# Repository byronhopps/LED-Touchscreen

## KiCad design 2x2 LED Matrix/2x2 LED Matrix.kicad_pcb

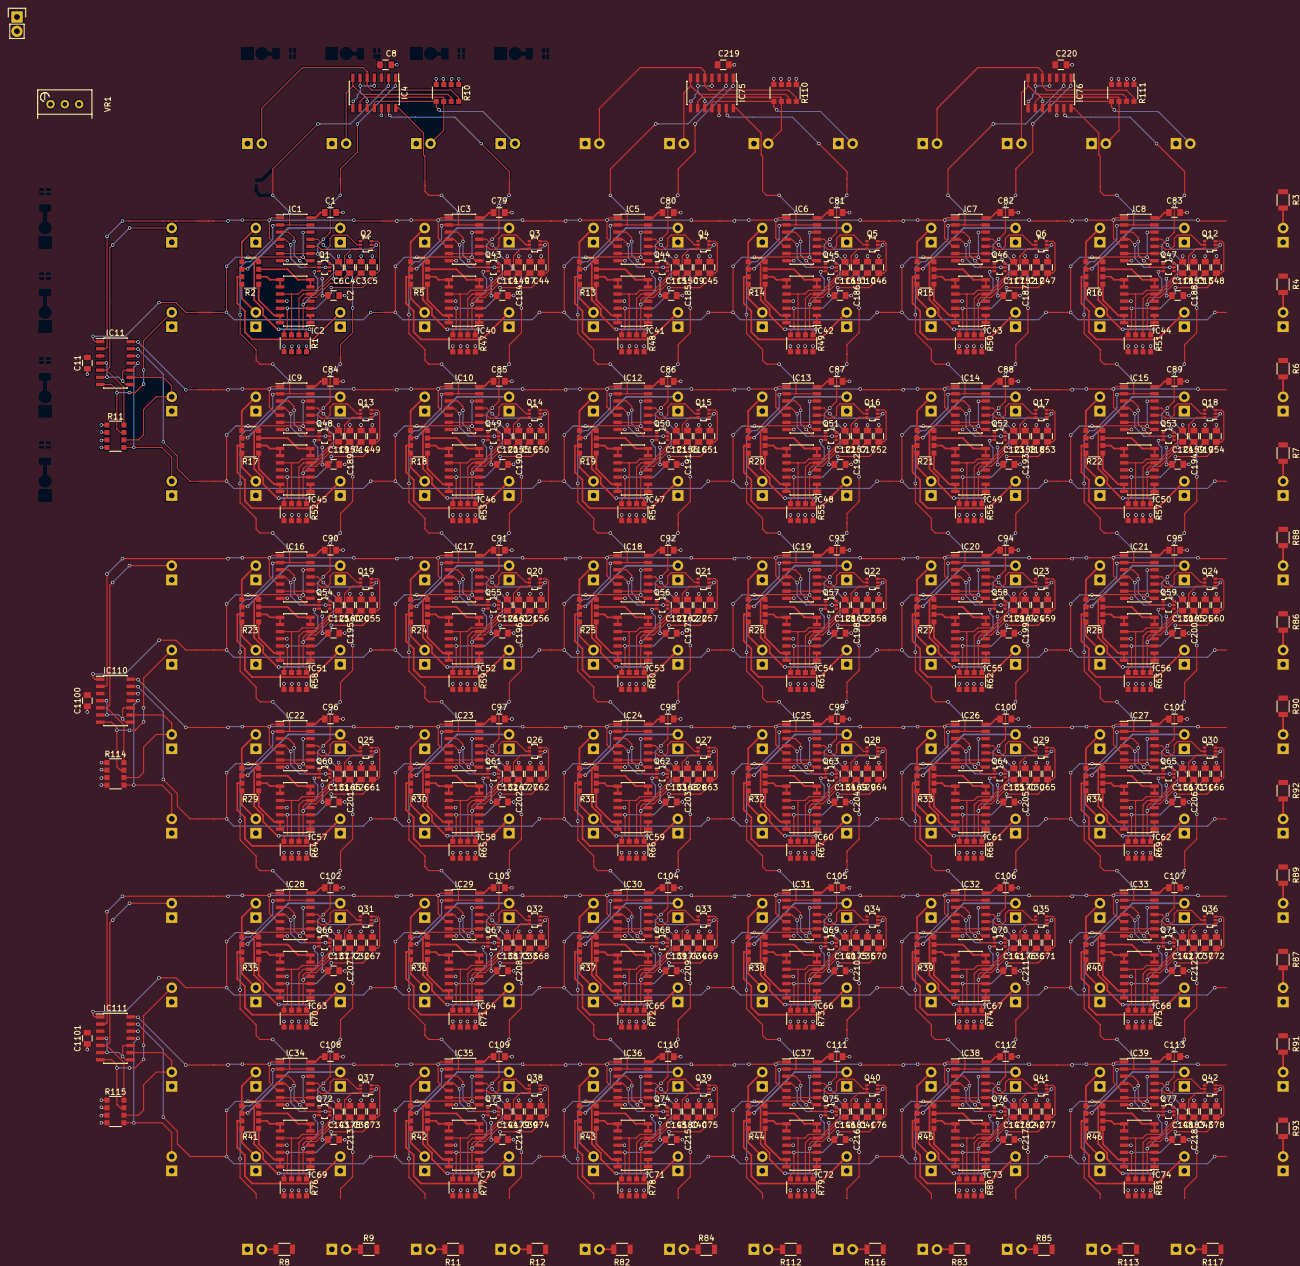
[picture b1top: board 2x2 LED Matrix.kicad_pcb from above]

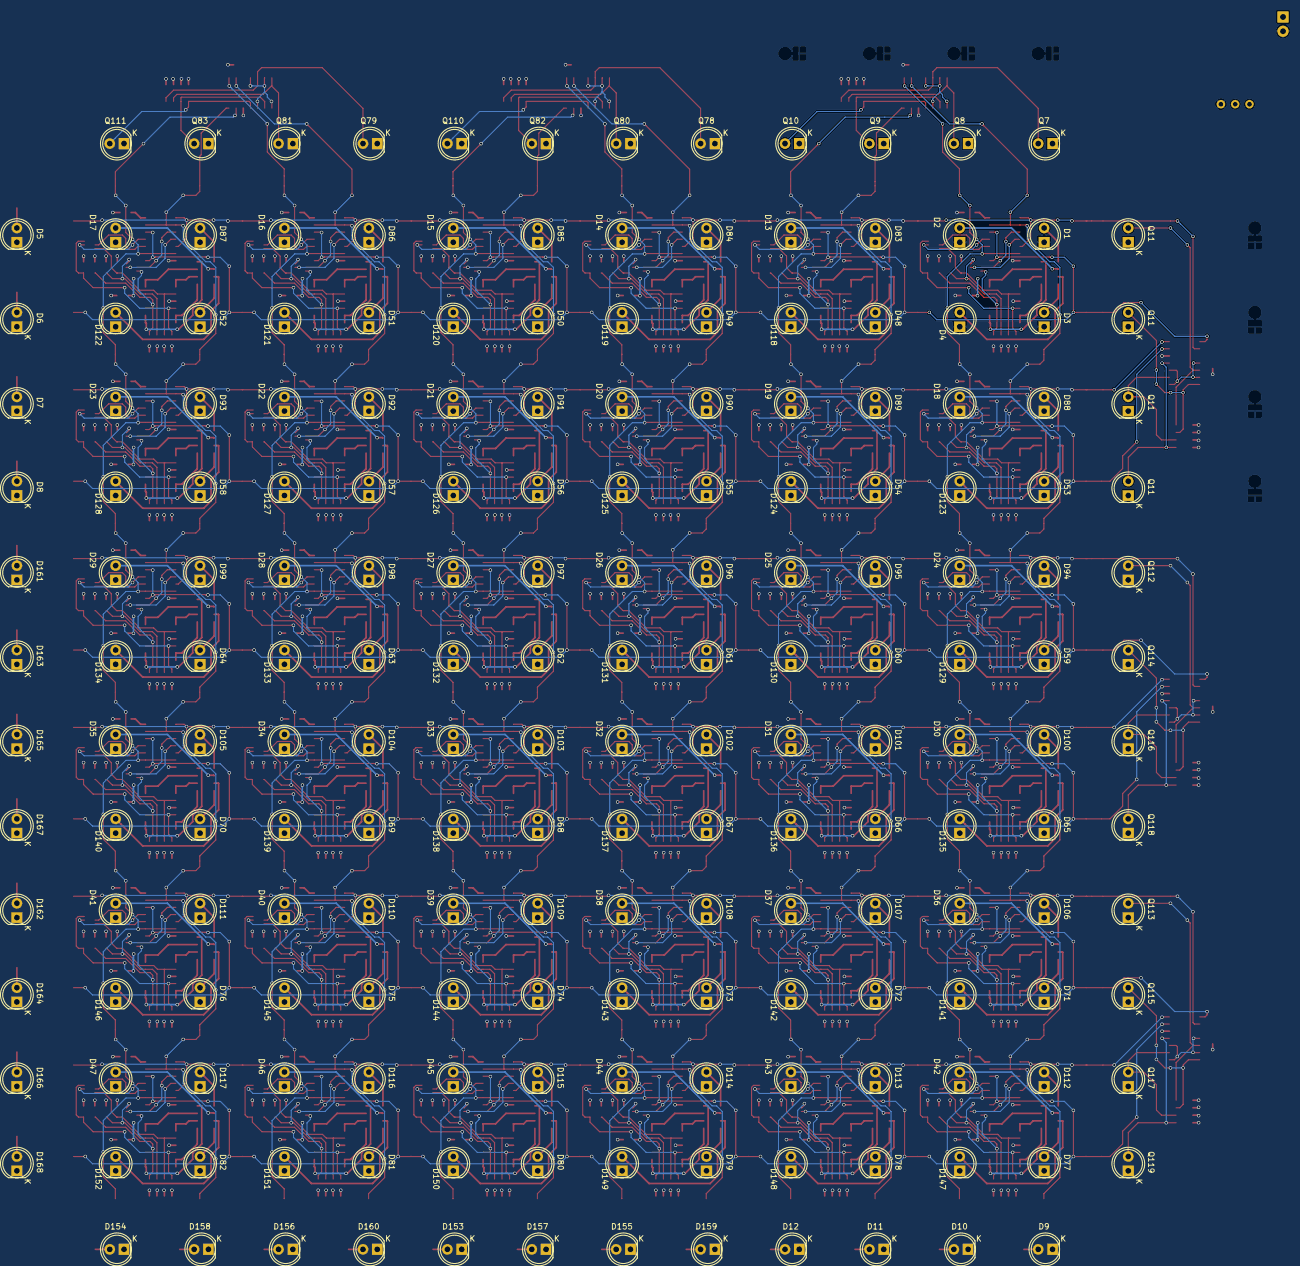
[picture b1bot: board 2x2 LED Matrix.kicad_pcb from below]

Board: 2 copper layers, 668 parts (192 on the bottom side), 47 nets.

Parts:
C1, C2, C8, C11, C79, C80, C81, C82, C83, C84, C85, C86, C87, C88, C89, C90, C91, C92, C93, C94, C95, C96, C97, C98, C99, C100, C101, C102, C103, C104, C105, C106, C107, C108, C109, C110, C111, C112, C113, C184, C185, C186, C187, C188, C189, C190, C191, C192, C193, C194, C195, C196, C197, C198, C199, C200, C201, C202, C203, C204, C205, C206, C207, C208, C209, C210, C211, C212, C213, C214, C215, C216, C217, C218, C219, C220, C1100, C1101: 100nF; C_0805
C3, C4, C5, C6, C7, C9, C10, C12, C13, C14, C15, C16, C17, C18, C19, C20, C21, C22, C23, C24, C25, C26, C27, C28, C29, C30, C31, C32, C33, C34, C35, C36, C37, C38, C39, C40, C41, C42, C43, C44, C45, C46, C47, C48, C49, C50, C51, C52, C53, C54, C55, C56, C57, C58, C59, C60, C61, C62, C63, C64, C65, C66, C67, C68, C69, C70, C71, C72, C73, C74, C75, C76, C77, C78, C114, C115, C116, C117, C118, C119, C120, C121, C122, C123, C124, C125, C126, C127, C128, C129, C130, C131, C132, C133, C134, C135, C136, C137, C138, C139, C140, C141, C142, C143, C144, C145, C146, C147, C148, C149, C150, C151, C152, C153, C154, C155, C156, C157, C158, C159, C160, C161, C162, C163, C164, C165, C166, C167, C168, C169, C170, C171, C172, C173, C174, C175, C176, C177, C178, C179, C180, C181, C182, C183: 1uF; C_0805
D1, D2, D3, D4, D13, D14, D15, D16, D17, D18, D19, D20, D21, D22, D23, D24, D25, D26, D27, D28, D29, D30, D31, D32, D33, D34, D35, D36, D37, D38, D39, D40, D41, D42, D43, D44, D45, D46, D47, D48, D49, D50, D51, D52, D53, D54, D55, D56, D57, D58, D59, D60, D61, D62, D63, D64, D65, D66, D67, D68, D69, D70, D71, D72, D73, D74, D75, D76, D77, D78, D79, D80, D81, D82, D83, D84, D85, D86, D87, D88, D89, D90, D91, D92, D93, D94, D95, D96, D97, D98, D99, D100, D101, D102, D103, D104, D105, D106, D107, D108, D109, D110, D111, D112, D113, D114, D115, D116, D117, D118, D119, D120, D121, D122, D123, D124, D125, D126, D127, D128, D129, D130, D131, D132, D133, D134, D135, D136, D137, D138, D139, D140, D141, D142, D143, D144, D145, D146, D147, D148, D149, D150, D151, D152: LED; LED-5MM
D5, D6, D7, D8, D9, D10, D11, D12, D153, D154, D155, D156, D157, D158, D159, D160, D161, D162, D163, D164, D165, D166, D167, D168: 850nm; LED-5MM
IC1, IC3, IC5, IC6, IC7, IC8, IC9, IC10, IC12, IC13, IC14, IC15, IC16, IC17, IC18, IC19, IC20, IC21, IC22, IC23, IC24, IC25, IC26, IC27, IC28, IC29, IC30, IC31, IC32, IC33, IC34, IC35, IC36, IC37, IC38, IC39: 4011; SOIC-14_3.9x8.7mm_Pitch1.27mm
IC2, IC40, IC41, IC42, IC43, IC44, IC45, IC46, IC47, IC48, IC49, IC50, IC51, IC52, IC53, IC54, IC55, IC56, IC57, IC58, IC59, IC60, IC61, IC62, IC63, IC64, IC65, IC66, IC67, IC68, IC69, IC70, IC71, IC72, IC73, IC74: LM324; SOIC-14_3.9x8.7mm_Pitch1.27mm
IC4, IC11, IC75, IC76, IC110, IC111: LM2901; SOIC-14_3.9x8.7mm_Pitch1.27mm
P1: PWR; Pin_Header_Straight_1x02
Q1, Q2, Q3, Q4, Q5, Q6, Q12, Q13, Q14, Q15, Q16, Q17, Q18, Q19, Q20, Q21, Q22, Q23, Q24, Q25, Q26, Q27, Q28, Q29, Q30, Q31, Q32, Q33, Q34, Q35, Q36, Q37, Q38, Q39, Q40, Q41, Q42, Q43, Q44, Q45, Q46, Q47, Q48, Q49, Q50, Q51, Q52, Q53, Q54, Q55, Q56, Q57, Q58, Q59, Q60, Q61, Q62, Q63, Q64, Q65, Q66, Q67, Q68, Q69, Q70, Q71, Q72, Q73, Q74, Q75, Q76, Q77: PMOS; TO-263
Q7, Q8, Q9, Q10, Q11, Q11#2, Q11#3, Q11#4, Q78, Q79, Q80, Q81, Q82, Q83, Q110, Q111, Q112, Q113, Q114, Q115, Q116, Q117, Q118, Q119: 850nm; LED-5MM
R1, R47, R48, R49, R50, R51, R52, R53, R54, R55, R56, R57, R58, R59, R60, R61, R62, R63, R64, R65, R66, R67, R68, R69, R70, R71, R72, R73, R74, R75, R76, R77, R78, R79, R80, R81: 220K; R_Array_Convex_4x1206
R2, R5, R13, R14, R15, R16, R17, R18, R19, R20, R21, R22, R23, R24, R25, R26, R27, R28, R29, R30, R31, R32, R33, R34, R35, R36, R37, R38, R39, R40, R41, R42, R43, R44, R45, R46: 470R; R_Array_Convex_4x1206
R3, R4, R6, R7, R8, R9, R11#2, R12, R82, R83, R84, R85, R86, R87, R88, R89, R90, R91, R92, R93, R112, R113, R116, R117: 120R; R_1206
R10, R11, R110, R111, R114, R115: 1K; R_Array_Convex_4x1206
VR1: 10K; Potentiometer_Bourns_3296W_3-8Zoll_Inline_ScrewUp

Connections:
+5V: C1.1, C2.1, C8.1, C11.1, C79.1, C80.1, C81.1, C82.1, C83.1, C84.1, C85.1, C86.1, C87.1, C88.1, C89.1, C90.1, C91.1, C92.1, C93.1, C94.1, C95.1, C96.1, C97.1, C98.1, C99.1, C100.1, C101.1, C102.1, C103.1, C104.1, C105.1, C106.1, C107.1, C108.1, C109.1, C110.1, C111.1, C112.1, C113.1, C184.1, C185.1, C186.1, C187.1, C188.1, C189.1, C190.1, C191.1, C192.1, C193.1, C194.1, C195.1, C196.1, C197.1, C198.1, C199.1, C200.1, C201.1, C202.1, C203.1, C204.1, C205.1, C206.1, C207.1, C208.1, C209.1, C210.1, C211.1, C212.1, C213.1, C214.1, C215.1, C216.1, C217.1, C218.1, C219.1, C220.1, C1100.1, C1101.1, IC1.14, IC2.4, IC3.14, IC4.3, IC5.14, IC6.14, IC7.14, IC8.14, IC9.14, IC10.14, IC11.3, IC12.14, IC13.14, IC14.14, IC15.14, IC16.14, IC17.14, IC18.14, IC19.14, IC20.14, IC21.14, IC22.14, IC23.14, IC24.14, IC25.14, IC26.14, IC27.14, IC28.14, IC29.14, IC30.14, IC31.14, IC32.14, IC33.14, IC34.14, IC35.14, IC36.14, IC37.14, IC38.14, IC39.14, IC40.4, IC41.4, IC42.4, IC43.4, IC44.4, IC45.4, IC46.4, IC47.4, IC48.4, IC49.4, IC50.4, IC51.4, IC52.4, IC53.4, IC54.4, IC55.4, IC56.4, IC57.4, IC58.4, IC59.4, IC60.4, IC61.4, IC62.4, IC63.4, IC64.4, IC65.4, IC66.4, IC67.4, IC68.4, IC69.4, IC70.4, IC71.4, IC72.4, IC73.4, IC74.4, IC75.3, IC76.3, IC110.3, IC111.3, P1.1, Q1.1, Q1.4, Q2.1, Q2.4, Q3.1, Q3.4, Q4.1, Q4.4, Q5.1, Q5.4, Q6.1, Q6.4, Q7.1, Q8.1, Q9.1, Q10.1, Q11.1, Q11#2.1, Q11#3.1, Q11#4.1, Q12.1, Q12.4, Q13.1, Q13.4, Q14.1, Q14.4, Q15.1, Q15.4, Q16.1, Q16.4, Q17.1, Q17.4, Q18.1, Q18.4, Q19.1, Q19.4, Q20.1, Q20.4, Q21.1, Q21.4, Q22.1, Q22.4, Q23.1, Q23.4, Q24.1, Q24.4, Q25.1, Q25.4, Q26.1, Q26.4, Q27.1, Q27.4, Q28.1, Q28.4, Q29.1, Q29.4, Q30.1, Q30.4, Q31.1, Q31.4, Q32.1, Q32.4, Q33.1, Q33.4, Q34.1, Q34.4, Q35.1, Q35.4, Q36.1, Q36.4, Q37.1, Q37.4, Q38.1, Q38.4, Q39.1, Q39.4, Q40.1, Q40.4, Q41.1, Q41.4, Q42.1, Q42.4, Q43.1, Q43.4, Q44.1, Q44.4, Q45.1, Q45.4, Q46.1, Q46.4, Q47.1, Q47.4, Q48.1, Q48.4, Q49.1, Q49.4, Q50.1, Q50.4, Q51.1, Q51.4, Q52.1, Q52.4, Q53.1, Q53.4, Q54.1, Q54.4, Q55.1, Q55.4, Q56.1, Q56.4, Q57.1, Q57.4, Q58.1, Q58.4, Q59.1, Q59.4, Q60.1, Q60.4, Q61.1, Q61.4, Q62.1, Q62.4, Q63.1, Q63.4, Q64.1, Q64.4, Q65.1, Q65.4, Q66.1, Q66.4, Q67.1, Q67.4, Q68.1, Q68.4, Q69.1, Q69.4, Q70.1, Q70.4, Q71.1, Q71.4, Q72.1, Q72.4, Q73.1, Q73.4, Q74.1, Q74.4, Q75.1, Q75.4, Q76.1, Q76.4, Q77.1, Q77.4, Q78.1, Q79.1, Q80.1, Q81.1, Q82.1, Q83.1, Q110.1, Q111.1, Q112.1, Q113.1, Q114.1, Q115.1, Q116.1, Q117.1, Q118.1, Q119.1, R3.1, R4.1, R6.1, R7.1, R8.1, R9.1, R11#2.1, R12.1, R82.1, R83.1, R84.1, R85.1, R86.1, R87.1, R88.1, R89.1, R90.1, R91.1, R92.1, R93.1, R112.1, R113.1, R116.1, R117.1, VR1.1
/Decay-1: C3.1, C7.1, C9.1, C10.1, C12.1, C13.1, C14.1, C15.1, C16.1, C17.1, C18.1, C19.1, C20.1, C21.1, C22.1, C23.1, C24.1, C25.1, C26.1, C27.1, C28.1, C29.1, C30.1, C31.1, C32.1, C33.1, C34.1, C35.1, C36.1, C37.1, C38.1, C39.1, C40.1, C41.1, C42.1, C43.1, IC2.3, IC40.3, IC41.3, IC42.3, IC43.3, IC44.3, IC45.3, IC46.3, IC47.3, IC48.3, IC49.3, IC50.3, IC51.3, IC52.3, IC53.3, IC54.3, IC55.3, IC56.3, IC57.3, IC58.3, IC59.3, IC60.3, IC61.3, IC62.3, IC63.3, IC64.3, IC65.3, IC66.3, IC67.3, IC68.3, IC69.3, IC70.3, IC71.3, IC72.3, IC73.3, IC74.3, Q1.3, Q43.3, Q44.3, Q45.3, Q46.3, Q47.3, Q48.3, Q49.3, Q50.3, Q51.3, Q52.3, Q53.3, Q54.3, Q55.3, Q56.3, Q57.3, Q58.3, Q59.3, Q60.3, Q61.3, Q62.3, Q63.3, Q64.3, Q65.3, Q66.3, Q67.3, Q68.3, Q69.3, Q70.3, Q71.3, Q72.3, Q73.3, Q74.3, Q75.3, Q76.3, Q77.3, R1.1, R47.1, R48.1, R49.1, R50.1, R51.1, R52.1, R53.1, R54.1, R55.1, R56.1, R57.1, R58.1, R59.1, R60.1, R61.1, R62.1, R63.1, R64.1, R65.1, R66.1, R67.1, R68.1, R69.1, R70.1, R71.1, R72.1, R73.1, R74.1, R75.1, R76.1, R77.1, R78.1, R79.1, R80.1, R81.1
/Decay-2: C4.1, C149.1, C150.1, C151.1, C152.1, C153.1, C154.1, C155.1, C156.1, C157.1, C158.1, C159.1, C160.1, C161.1, C162.1, C163.1, C164.1, C165.1, C166.1, C167.1, C168.1, C169.1, C170.1, C171.1, C172.1, C173.1, C174.1, C175.1, C176.1, C177.1, C178.1, C179.1, C180.1, C181.1, C182.1, C183.1, IC2.5, IC40.5, IC41.5, IC42.5, IC43.5, IC44.5, IC45.5, IC46.5, IC47.5, IC48.5, IC49.5, IC50.5, IC51.5, IC52.5, IC53.5, IC54.5, IC55.5, IC56.5, IC57.5, IC58.5, IC59.5, IC60.5, IC61.5, IC62.5, IC63.5, IC64.5, IC65.5, IC66.5, IC67.5, IC68.5, IC69.5, IC70.5, IC71.5, IC72.5, IC73.5, IC74.5, Q1.6, Q43.6, Q44.6, Q45.6, Q46.6, Q47.6, Q48.6, Q49.6, Q50.6, Q51.6, Q52.6, Q53.6, Q54.6, Q55.6, Q56.6, Q57.6, Q58.6, Q59.6, Q60.6, Q61.6, Q62.6, Q63.6, Q64.6, Q65.6, Q66.6, Q67.6, Q68.6, Q69.6, Q70.6, Q71.6, Q72.6, Q73.6, Q74.6, Q75.6, Q76.6, Q77.6, R1.2, R47.2, R48.2, R49.2, R50.2, R51.2, R52.2, R53.2, R54.2, R55.2, R56.2, R57.2, R58.2, R59.2, R60.2, R61.2, R62.2, R63.2, R64.2, R65.2, R66.2, R67.2, R68.2, R69.2, R70.2, R71.2, R72.2, R73.2, R74.2, R75.2, R76.2, R77.2, R78.2, R79.2, R80.2, R81.2
/Decay-3: C5.1, C44.1, C45.1, C46.1, C47.1, C48.1, C49.1, C50.1, C51.1, C52.1, C53.1, C54.1, C55.1, C56.1, C57.1, C58.1, C59.1, C60.1, C61.1, C62.1, C63.1, C64.1, C65.1, C66.1, C67.1, C68.1, C69.1, C70.1, C71.1, C72.1, C73.1, C74.1, C75.1, C76.1, C77.1, C78.1, IC2.12, IC40.12, IC41.12, IC42.12, IC43.12, IC44.12, IC45.12, IC46.12, IC47.12, IC48.12, IC49.12, IC50.12, IC51.12, IC52.12, IC53.12, IC54.12, IC55.12, IC56.12, IC57.12, IC58.12, IC59.12, IC60.12, IC61.12, IC62.12, IC63.12, IC64.12, IC65.12, IC66.12, IC67.12, IC68.12, IC69.12, IC70.12, IC71.12, IC72.12, IC73.12, IC74.12, Q2.3, Q3.3, Q4.3, Q5.3, Q6.3, Q12.3, Q13.3, Q14.3, Q15.3, Q16.3, Q17.3, Q18.3, Q19.3, Q20.3, Q21.3, Q22.3, Q23.3, Q24.3, Q25.3, Q26.3, Q27.3, Q28.3, Q29.3, Q30.3, Q31.3, Q32.3, Q33.3, Q34.3, Q35.3, Q36.3, Q37.3, Q38.3, Q39.3, Q40.3, Q41.3, Q42.3, R1.4, R47.4, R48.4, R49.4, R50.4, R51.4, R52.4, R53.4, R54.4, R55.4, R56.4, R57.4, R58.4, R59.4, R60.4, R61.4, R62.4, R63.4, R64.4, R65.4, R66.4, R67.4, R68.4, R69.4, R70.4, R71.4, R72.4, R73.4, R74.4, R75.4, R76.4, R77.4, R78.4, R79.4, R80.4, R81.4
/Decay-4: C6.1, C114.1, C115.1, C116.1, C117.1, C118.1, C119.1, C120.1, C121.1, C122.1, C123.1, C124.1, C125.1, C126.1, C127.1, C128.1, C129.1, C130.1, C131.1, C132.1, C133.1, C134.1, C135.1, C136.1, C137.1, C138.1, C139.1, C140.1, C141.1, C142.1, C143.1, C144.1, C145.1, C146.1, C147.1, C148.1, IC2.10, IC40.10, IC41.10, IC42.10, IC43.10, IC44.10, IC45.10, IC46.10, IC47.10, IC48.10, IC49.10, IC50.10, IC51.10, IC52.10, IC53.10, IC54.10, IC55.10, IC56.10, IC57.10, IC58.10, IC59.10, IC60.10, IC61.10, IC62.10, IC63.10, IC64.10, IC65.10, IC66.10, IC67.10, IC68.10, IC69.10, IC70.10, IC71.10, IC72.10, IC73.10, IC74.10, Q2.6, Q3.6, Q4.6, Q5.6, Q6.6, Q12.6, Q13.6, Q14.6, Q15.6, Q16.6, Q17.6, Q18.6, Q19.6, Q20.6, Q21.6, Q22.6, Q23.6, Q24.6, Q25.6, Q26.6, Q27.6, Q28.6, Q29.6, Q30.6, Q31.6, Q32.6, Q33.6, Q34.6, Q35.6, Q36.6, Q37.6, Q38.6, Q39.6, Q40.6, Q41.6, Q42.6, R1.3, R47.3, R48.3, R49.3, R50.3, R51.3, R52.3, R53.3, R54.3, R55.3, R56.3, R57.3, R58.3, R59.3, R60.3, R61.3, R62.3, R63.3, R64.3, R65.3, R66.3, R67.3, R68.3, R69.3, R70.3, R71.3, R72.3, R73.3, R74.3, R75.3, R76.3, R77.3, R78.3, R79.3, R80.3, R81.3
/Detector X/Detect-1: IC4.5, IC75.5, IC76.5, Q7.2, Q78.2, Q79.2, R10.8, R110.8, R111.8
/Detector X/Detect-2: IC4.7, IC75.7, IC76.7, Q8.2, Q80.2, Q81.2, R10.7, R110.7, R111.7
/Detector X/Detect-3: IC4.9, IC75.9, IC76.9, Q9.2, Q82.2, Q83.2, R10.6, R110.6, R111.6
/Detector X/Detect-4: IC4.11, IC75.11, IC76.11, Q10.2, Q110.2, Q111.2, R10.5, R110.5, R111.5
/Detector X/Out-1: IC4.2, IC75.2, IC76.2
/Detector X/Out-2: IC4.1, IC75.1, IC76.1
/Detector X/Out-3: IC4.14, IC75.14, IC76.14
/Detector X/Out-4: IC4.13, IC75.13, IC76.13
/Detector Y/Detect-1: IC11.5, IC110.5, IC111.5, Q11.2, Q112.2, Q113.2, R11.8, R114.8, R115.8
/Detector Y/Detect-2: IC11.7, IC110.7, IC111.7, Q11#2.2, Q114.2, Q115.2, R11.7, R114.7, R115.7
/Detector Y/Detect-3: IC11.9, IC110.9, IC111.9, Q11#3.2, Q116.2, Q117.2, R11.6, R114.6, R115.6
/Detector Y/Detect-4: IC11.11, IC110.11, IC111.11, Q11#4.2, Q118.2, Q119.2, R11.5, R114.5, R115.5
/Detector Y/Out-1: IC11.2, IC110.2, IC111.2
/Detector Y/Out-2: IC11.1, IC110.1, IC111.1
/Detector Y/Out-3: IC11.14, IC110.14, IC111.14
/Detector Y/Out-4: IC11.13, IC110.13, IC111.13
/LED1: IC2.1, IC2.2, IC40.1, IC40.2, IC41.1, IC41.2, IC42.1, IC42.2, IC43.1, IC43.2, IC44.1, IC44.2, IC45.1, IC45.2, IC46.1, IC46.2, IC47.1, IC47.2, IC48.1, IC48.2, IC49.1, IC49.2, IC50.1, IC50.2, IC51.1, IC51.2, IC52.1, IC52.2, IC53.1, IC53.2, IC54.1, IC54.2, IC55.1, IC55.2, IC56.1, IC56.2, IC57.1, IC57.2, IC58.1, IC58.2, IC59.1, IC59.2, IC60.1, IC60.2, IC61.1, IC61.2, IC62.1, IC62.2, IC63.1, IC63.2, IC64.1, IC64.2, IC65.1, IC65.2, IC66.1, IC66.2, IC67.1, IC67.2, IC68.1, IC68.2, IC69.1, IC69.2, IC70.1, IC70.2, IC71.1, IC71.2, IC72.1, IC72.2, IC73.1, IC73.2, IC74.1, IC74.2, R2.4, R5.4, R13.4, R14.4, R15.4, R16.4, R17.4, R18.4, R19.4, R20.4, R21.4, R22.4, R23.4, R24.4, R25.4, R26.4, R27.4, R28.4, R29.4, R30.4, R31.4, R32.4, R33.4, R34.4, R35.4, R36.4, R37.4, R38.4, R39.4, R40.4, R41.4, R42.4, R43.4, R44.4, R45.4, R46.4
/LED2: IC2.6, IC2.7, IC40.6, IC40.7, IC41.6, IC41.7, IC42.6, IC42.7, IC43.6, IC43.7, IC44.6, IC44.7, IC45.6, IC45.7, IC46.6, IC46.7, IC47.6, IC47.7, IC48.6, IC48.7, IC49.6, IC49.7, IC50.6, IC50.7, IC51.6, IC51.7, IC52.6, IC52.7, IC53.6, IC53.7, IC54.6, IC54.7, IC55.6, IC55.7, IC56.6, IC56.7, IC57.6, IC57.7, IC58.6, IC58.7, IC59.6, IC59.7, IC60.6, IC60.7, IC61.6, IC61.7, IC62.6, IC62.7, IC63.6, IC63.7, IC64.6, IC64.7, IC65.6, IC65.7, IC66.6, IC66.7, IC67.6, IC67.7, IC68.6, IC68.7, IC69.6, IC69.7, IC70.6, IC70.7, IC71.6, IC71.7, IC72.6, IC72.7, IC73.6, IC73.7, IC74.6, IC74.7, R2.3, R5.3, R13.3, R14.3, R15.3, R16.3, R17.3, R18.3, R19.3, R20.3, R21.3, R22.3, R23.3, R24.3, R25.3, R26.3, R27.3, R28.3, R29.3, R30.3, R31.3, R32.3, R33.3, R34.3, R35.3, R36.3, R37.3, R38.3, R39.3, R40.3, R41.3, R42.3, R43.3, R44.3, R45.3, R46.3
/LED3: IC2.13, IC2.14, IC40.13, IC40.14, IC41.13, IC41.14, IC42.13, IC42.14, IC43.13, IC43.14, IC44.13, IC44.14, IC45.13, IC45.14, IC46.13, IC46.14, IC47.13, IC47.14, IC48.13, IC48.14, IC49.13, IC49.14, IC50.13, IC50.14, IC51.13, IC51.14, IC52.13, IC52.14, IC53.13, IC53.14, IC54.13, IC54.14, IC55.13, IC55.14, IC56.13, IC56.14, IC57.13, IC57.14, IC58.13, IC58.14, IC59.13, IC59.14, IC60.13, IC60.14, IC61.13, IC61.14, IC62.13, IC62.14, IC63.13, IC63.14, IC64.13, IC64.14, IC65.13, IC65.14, IC66.13, IC66.14, IC67.13, IC67.14, IC68.13, IC68.14, IC69.13, IC69.14, IC70.13, IC70.14, IC71.13, IC71.14, IC72.13, IC72.14, IC73.13, IC73.14, IC74.13, IC74.14, R2.1, R5.1, R13.1, R14.1, R15.1, R16.1, R17.1, R18.1, R19.1, R20.1, R21.1, R22.1, R23.1, R24.1, R25.1, R26.1, R27.1, R28.1, R29.1, R30.1, R31.1, R32.1, R33.1, R34.1, R35.1, R36.1, R37.1, R38.1, R39.1, R40.1, R41.1, R42.1, R43.1, R44.1, R45.1, R46.1
/LED4: IC2.8, IC2.9, IC40.8, IC40.9, IC41.8, IC41.9, IC42.8, IC42.9, IC43.8, IC43.9, IC44.8, IC44.9, IC45.8, IC45.9, IC46.8, IC46.9, IC47.8, IC47.9, IC48.8, IC48.9, IC49.8, IC49.9, IC50.8, IC50.9, IC51.8, IC51.9, IC52.8, IC52.9, IC53.8, IC53.9, IC54.8, IC54.9, IC55.8, IC55.9, IC56.8, IC56.9, IC57.8, IC57.9, IC58.8, IC58.9, IC59.8, IC59.9, IC60.8, IC60.9, IC61.8, IC61.9, IC62.8, IC62.9, IC63.8, IC63.9, IC64.8, IC64.9, IC65.8, IC65.9, IC66.8, IC66.9, IC67.8, IC67.9, IC68.8, IC68.9, IC69.8, IC69.9, IC70.8, IC70.9, IC71.8, IC71.9, IC72.8, IC72.9, IC73.8, IC73.9, IC74.8, IC74.9, R2.2, R5.2, R13.2, R14.2, R15.2, R16.2, R17.2, R18.2, R19.2, R20.2, R21.2, R22.2, R23.2, R24.2, R25.2, R26.2, R27.2, R28.2, R29.2, R30.2, R31.2, R32.2, R33.2, R34.2, R35.2, R36.2, R37.2, R38.2, R39.2, R40.2, R41.2, R42.2, R43.2, R44.2, R45.2, R46.2
/On-1: IC1.3, IC3.3, IC5.3, IC6.3, IC7.3, IC8.3, IC9.3, IC10.3, IC12.3, IC13.3, IC14.3, IC15.3, IC16.3, IC17.3, IC18.3, IC19.3, IC20.3, IC21.3, IC22.3, IC23.3, IC24.3, IC25.3, IC26.3, IC27.3, IC28.3, IC29.3, IC30.3, IC31.3, IC32.3, IC33.3, IC34.3, IC35.3, IC36.3, IC37.3, IC38.3, IC39.3, Q1.2, Q43.2, Q44.2, Q45.2, Q46.2, Q47.2, Q48.2, Q49.2, Q50.2, Q51.2, Q52.2, Q53.2, Q54.2, Q55.2, Q56.2, Q57.2, Q58.2, Q59.2, Q60.2, Q61.2, Q62.2, Q63.2, Q64.2, Q65.2, Q66.2, Q67.2, Q68.2, Q69.2, Q70.2, Q71.2, Q72.2, Q73.2, Q74.2, Q75.2, Q76.2, Q77.2
/On-2: IC1.4, IC3.4, IC5.4, IC6.4, IC7.4, IC8.4, IC9.4, IC10.4, IC12.4, IC13.4, IC14.4, IC15.4, IC16.4, IC17.4, IC18.4, IC19.4, IC20.4, IC21.4, IC22.4, IC23.4, IC24.4, IC25.4, IC26.4, IC27.4, IC28.4, IC29.4, IC30.4, IC31.4, IC32.4, IC33.4, IC34.4, IC35.4, IC36.4, IC37.4, IC38.4, IC39.4, Q1.5, Q43.5, Q44.5, Q45.5, Q46.5, Q47.5, Q48.5, Q49.5, Q50.5, Q51.5, Q52.5, Q53.5, Q54.5, Q55.5, Q56.5, Q57.5, Q58.5, Q59.5, Q60.5, Q61.5, Q62.5, Q63.5, Q64.5, Q65.5, Q66.5, Q67.5, Q68.5, Q69.5, Q70.5, Q71.5, Q72.5, Q73.5, Q74.5, Q75.5, Q76.5, Q77.5
/On-3: IC1.11, IC3.11, IC5.11, IC6.11, IC7.11, IC8.11, IC9.11, IC10.11, IC12.11, IC13.11, IC14.11, IC15.11, IC16.11, IC17.11, IC18.11, IC19.11, IC20.11, IC21.11, IC22.11, IC23.11, IC24.11, IC25.11, IC26.11, IC27.11, IC28.11, IC29.11, IC30.11, IC31.11, IC32.11, IC33.11, IC34.11, IC35.11, IC36.11, IC37.11, IC38.11, IC39.11, Q2.2, Q3.2, Q4.2, Q5.2, Q6.2, Q12.2, Q13.2, Q14.2, Q15.2, Q16.2, Q17.2, Q18.2, Q19.2, Q20.2, Q21.2, Q22.2, Q23.2, Q24.2, Q25.2, Q26.2, Q27.2, Q28.2, Q29.2, Q30.2, Q31.2, Q32.2, Q33.2, Q34.2, Q35.2, Q36.2, Q37.2, Q38.2, Q39.2, Q40.2, Q41.2, Q42.2
/On-4: IC1.10, IC3.10, IC5.10, IC6.10, IC7.10, IC8.10, IC9.10, IC10.10, IC12.10, IC13.10, IC14.10, IC15.10, IC16.10, IC17.10, IC18.10, IC19.10, IC20.10, IC21.10, IC22.10, IC23.10, IC24.10, IC25.10, IC26.10, IC27.10, IC28.10, IC29.10, IC30.10, IC31.10, IC32.10, IC33.10, IC34.10, IC35.10, IC36.10, IC37.10, IC38.10, IC39.10, Q2.5, Q3.5, Q4.5, Q5.5, Q6.5, Q12.5, Q13.5, Q14.5, Q15.5, Q16.5, Q17.5, Q18.5, Q19.5, Q20.5, Q21.5, Q22.5, Q23.5, Q24.5, Q25.5, Q26.5, Q27.5, Q28.5, Q29.5, Q30.5, Q31.5, Q32.5, Q33.5, Q34.5, Q35.5, Q36.5, Q37.5, Q38.5, Q39.5, Q40.5, Q41.5, Q42.5
/X1: IC1.2, IC1.13, IC3.2, IC3.13, IC5.2, IC5.13, IC6.2, IC6.13, IC7.2, IC7.13, IC8.2, IC8.13, IC9.2, IC9.13, IC10.2, IC10.13, IC12.2, IC12.13, IC13.2, IC13.13, IC14.2, IC14.13, IC15.2, IC15.13, IC16.2, IC16.13, IC17.2, IC17.13, IC18.2, IC18.13, IC19.2, IC19.13, IC20.2, IC20.13, IC21.2, IC21.13, IC22.2, IC22.13, IC23.2, IC23.13, IC24.2, IC24.13, IC25.2, IC25.13, IC26.2, IC26.13, IC27.2, IC27.13, IC28.2, IC28.13, IC29.2, IC29.13, IC30.2, IC30.13, IC31.2, IC31.13, IC32.2, IC32.13, IC33.2, IC33.13, IC34.2, IC34.13, IC35.2, IC35.13, IC36.2, IC36.13, IC37.2, IC37.13, IC38.2, IC38.13, IC39.2, IC39.13
/X2: IC1.6, IC1.9, IC3.6, IC3.9, IC5.6, IC5.9, IC6.6, IC6.9, IC7.6, IC7.9, IC8.6, IC8.9, IC9.6, IC9.9, IC10.6, IC10.9, IC12.6, IC12.9, IC13.6, IC13.9, IC14.6, IC14.9, IC15.6, IC15.9, IC16.6, IC16.9, IC17.6, IC17.9, IC18.6, IC18.9, IC19.6, IC19.9, IC20.6, IC20.9, IC21.6, IC21.9, IC22.6, IC22.9, IC23.6, IC23.9, IC24.6, IC24.9, IC25.6, IC25.9, IC26.6, IC26.9, IC27.6, IC27.9, IC28.6, IC28.9, IC29.6, IC29.9, IC30.6, IC30.9, IC31.6, IC31.9, IC32.6, IC32.9, IC33.6, IC33.9, IC34.6, IC34.9, IC35.6, IC35.9, IC36.6, IC36.9, IC37.6, IC37.9, IC38.6, IC38.9, IC39.6, IC39.9
/Y1: IC1.1, IC1.5, IC3.1, IC3.5, IC5.1, IC5.5, IC6.1, IC6.5, IC7.1, IC7.5, IC8.1, IC8.5, IC9.1, IC9.5, IC10.1, IC10.5, IC12.1, IC12.5, IC13.1, IC13.5, IC14.1, IC14.5, IC15.1, IC15.5, IC16.1, IC16.5, IC17.1, IC17.5, IC18.1, IC18.5, IC19.1, IC19.5, IC20.1, IC20.5, IC21.1, IC21.5, IC22.1, IC22.5, IC23.1, IC23.5, IC24.1, IC24.5, IC25.1, IC25.5, IC26.1, IC26.5, IC27.1, IC27.5, IC28.1, IC28.5, IC29.1, IC29.5, IC30.1, IC30.5, IC31.1, IC31.5, IC32.1, IC32.5, IC33.1, IC33.5, IC34.1, IC34.5, IC35.1, IC35.5, IC36.1, IC36.5, IC37.1, IC37.5, IC38.1, IC38.5, IC39.1, IC39.5
/Y2: IC1.8, IC1.12, IC3.8, IC3.12, IC5.8, IC5.12, IC6.8, IC6.12, IC7.8, IC7.12, IC8.8, IC8.12, IC9.8, IC9.12, IC10.8, IC10.12, IC12.8, IC12.12, IC13.8, IC13.12, IC14.8, IC14.12, IC15.8, IC15.12, IC16.8, IC16.12, IC17.8, IC17.12, IC18.8, IC18.12, IC19.8, IC19.12, IC20.8, IC20.12, IC21.8, IC21.12, IC22.8, IC22.12, IC23.8, IC23.12, IC24.8, IC24.12, IC25.8, IC25.12, IC26.8, IC26.12, IC27.8, IC27.12, IC28.8, IC28.12, IC29.8, IC29.12, IC30.8, IC30.12, IC31.8, IC31.12, IC32.8, IC32.12, IC33.8, IC33.12, IC34.8, IC34.12, IC35.8, IC35.12, IC36.8, IC36.12, IC37.8, IC37.12, IC38.8, IC38.12, IC39.8, IC39.12
GND: C1.2, C2.2, C3.2, C4.2, C5.2, C6.2, C7.2, C8.2, C9.2, C10.2, C11.2, C12.2, C13.2, C14.2, C15.2, C16.2, C17.2, C18.2, C19.2, C20.2, C21.2, C22.2, C23.2, C24.2, C25.2, C26.2, C27.2, C28.2, C29.2, C30.2, C31.2, C32.2, C33.2, C34.2, C35.2, C36.2, C37.2, C38.2, C39.2, C40.2, C41.2, C42.2, C43.2, C44.2, C45.2, C46.2, C47.2, C48.2, C49.2, C50.2, C51.2, C52.2, C53.2, C54.2, C55.2, C56.2, C57.2, C58.2, C59.2, C60.2, C61.2, C62.2, C63.2, C64.2, C65.2, C66.2, C67.2, C68.2, C69.2, C70.2, C71.2, C72.2, C73.2, C74.2, C75.2, C76.2, C77.2, C78.2, C79.2, C80.2, C81.2, C82.2, C83.2, C84.2, C85.2, C86.2, C87.2, C88.2, C89.2, C90.2, C91.2, C92.2, C93.2, C94.2, C95.2, C96.2, C97.2, C98.2, C99.2, C100.2, C101.2, C102.2, C103.2, C104.2, C105.2, C106.2, C107.2, C108.2, C109.2, C110.2, C111.2, C112.2, C113.2, C114.2, C115.2, C116.2, C117.2, C118.2, C119.2, C120.2, C121.2, C122.2, C123.2, C124.2, C125.2, C126.2, C127.2, C128.2, C129.2, C130.2, C131.2, C132.2, C133.2, C134.2, C135.2, C136.2, C137.2, C138.2, C139.2, C140.2, C141.2, C142.2, C143.2, C144.2, C145.2, C146.2, C147.2, C148.2, C149.2, C150.2, C151.2, C152.2, C153.2, C154.2, C155.2, C156.2, C157.2, C158.2, C159.2, C160.2, C161.2, C162.2, C163.2, C164.2, C165.2, C166.2, C167.2, C168.2, C169.2, C170.2, C171.2, C172.2, C173.2, C174.2, C175.2, C176.2, C177.2, C178.2, C179.2, C180.2, C181.2, C182.2, C183.2, C184.2, C185.2, C186.2, C187.2, C188.2, C189.2, C190.2, C191.2, C192.2, C193.2, C194.2, C195.2, C196.2, C197.2, C198.2, C199.2, C200.2, C201.2, C202.2, C203.2, C204.2, C205.2, C206.2, C207.2, C208.2, C209.2, C210.2, C211.2, C212.2, C213.2, C214.2, C215.2, C216.2, C217.2, C218.2, C219.2, C220.2, C1100.2, C1101.2, D1.1, D2.1, D3.1, D4.1, D5.1, D6.1, D7.1, D8.1, D9.1, D10.1, D11.1, D12.1, D13.1, D14.1, D15.1, D16.1, D17.1, D18.1, D19.1, D20.1, D21.1, D22.1, D23.1, D24.1, D25.1, D26.1, D27.1, D28.1, D29.1, D30.1, D31.1, D32.1, D33.1, D34.1, D35.1, D36.1, D37.1, D38.1, D39.1, D40.1, D41.1, D42.1, D43.1, D44.1, D45.1, D46.1, D47.1, D48.1, D49.1, D50.1, D51.1, D52.1, D53.1, D54.1, D55.1, D56.1, D57.1, D58.1, D59.1, D60.1, D61.1, D62.1, D63.1, D64.1, D65.1, D66.1, D67.1, D68.1, D69.1, D70.1, D71.1, D72.1, D73.1, D74.1, D75.1, D76.1, D77.1, D78.1, D79.1, D80.1, D81.1, D82.1, D83.1, D84.1, D85.1, D86.1, D87.1, D88.1, D89.1, D90.1, D91.1, D92.1, D93.1, D94.1, D95.1, D96.1, D97.1, D98.1, D99.1, D100.1, D101.1, D102.1, D103.1, D104.1, D105.1, D106.1, D107.1, D108.1, D109.1, D110.1, D111.1, D112.1, D113.1, D114.1, D115.1, D116.1, D117.1, D118.1, D119.1, D120.1, D121.1, D122.1, D123.1, D124.1, D125.1, D126.1, D127.1, D128.1, D129.1, D130.1, D131.1, D132.1, D133.1, D134.1, D135.1, D136.1, D137.1, D138.1, D139.1, D140.1, D141.1, D142.1, D143.1, D144.1, D145.1, D146.1, D147.1, D148.1, D149.1, D150.1, D151.1, D152.1, D153.1, D154.1, D155.1, D156.1, D157.1, D158.1, D159.1, D160.1, D161.1, D162.1, D163.1, D164.1, D165.1, D166.1, D167.1, D168.1, IC1.7, IC2.11, IC3.7, IC4.12, IC5.7, IC6.7, IC7.7, IC8.7, IC9.7, IC10.7, IC11.12, IC12.7, IC13.7, IC14.7, IC15.7, IC16.7, IC17.7, IC18.7, IC19.7, IC20.7, IC21.7, IC22.7, IC23.7, IC24.7, IC25.7, IC26.7, IC27.7, IC28.7, IC29.7, IC30.7, IC31.7, IC32.7, IC33.7, IC34.7, IC35.7, IC36.7, IC37.7, IC38.7, IC39.7, IC40.11, IC41.11, IC42.11, IC43.11, IC44.11, IC45.11, IC46.11, IC47.11, IC48.11, IC49.11, IC50.11, IC51.11, IC52.11, IC53.11, IC54.11, IC55.11, IC56.11, IC57.11, IC58.11, IC59.11, IC60.11, IC61.11, IC62.11, IC63.11, IC64.11, IC65.11, IC66.11, IC67.11, IC68.11, IC69.11, IC70.11, IC71.11, IC72.11, IC73.11, IC74.11, IC75.12, IC76.12, IC110.12, IC111.12, P1.2, R1.5, R1.6, R1.7, R1.8, R10.1, R10.2, R10.3, R10.4, R11.1, R11.2, R11.3, R11.4, R47.5, R47.6, R47.7, R47.8, R48.5, R48.6, R48.7, R48.8, R49.5, R49.6, R49.7, R49.8, R50.5, R50.6, R50.7, R50.8, R51.5, R51.6, R51.7, R51.8, R52.5, R52.6, R52.7, R52.8, R53.5, R53.6, R53.7, R53.8, R54.5, R54.6, R54.7, R54.8, R55.5, R55.6, R55.7, R55.8, R56.5, R56.6, R56.7, R56.8, R57.5, R57.6, R57.7, R57.8, R58.5, R58.6, R58.7, R58.8, R59.5, R59.6, R59.7, R59.8, R60.5, R60.6, R60.7, R60.8, R61.5, R61.6, R61.7, R61.8, R62.5, R62.6, R62.7, R62.8, R63.5, R63.6, R63.7, R63.8, R64.5, R64.6, R64.7, R64.8, R65.5, R65.6, R65.7, R65.8, R66.5, R66.6, R66.7, R66.8, R67.5, R67.6, R67.7, R67.8, R68.5, R68.6, R68.7, R68.8, R69.5, R69.6, R69.7, R69.8, R70.5, R70.6, R70.7, R70.8, R71.5, R71.6, R71.7, R71.8, R72.5, R72.6, R72.7, R72.8, R73.5, R73.6, R73.7, R73.8, R74.5, R74.6, R74.7, R74.8, R75.5, R75.6, R75.7, R75.8, R76.5, R76.6, R76.7, R76.8, R77.5, R77.6, R77.7, R77.8, R78.5, R78.6, R78.7, R78.8, R79.5, R79.6, R79.7, R79.8, R80.5, R80.6, R80.7, R80.8, R81.5, R81.6, R81.7, R81.8, R110.1, R110.2, R110.3, R110.4, R111.1, R111.2, R111.3, R111.4, R114.1, R114.2, R114.3, R114.4, R115.1, R115.2, R115.3, R115.4, VR1.3
unnamed: D1.2, D83.2, D84.2, D85.2, D86.2, D87.2, D88.2, D89.2, D90.2, D91.2, D92.2, D93.2, D94.2, D95.2, D96.2, D97.2, D98.2, D99.2, D100.2, D101.2, D102.2, D103.2, D104.2, D105.2, D106.2, D107.2, D108.2, D109.2, D110.2, D111.2, D112.2, D113.2, D114.2, D115.2, D116.2, D117.2, R2.5, R5.5, R13.5, R14.5, R15.5, R16.5, R17.5, R18.5, R19.5, R20.5, R21.5, R22.5, R23.5, R24.5, R25.5, R26.5, R27.5, R28.5, R29.5, R30.5, R31.5, R32.5, R33.5, R34.5, R35.5, R36.5, R37.5, R38.5, R39.5, R40.5, R41.5, R42.5, R43.5, R44.5, R45.5, R46.5
unnamed: D2.2, D13.2, D14.2, D15.2, D16.2, D17.2, D18.2, D19.2, D20.2, D21.2, D22.2, D23.2, D24.2, D25.2, D26.2, D27.2, D28.2, D29.2, D30.2, D31.2, D32.2, D33.2, D34.2, D35.2, D36.2, D37.2, D38.2, D39.2, D40.2, D41.2, D42.2, D43.2, D44.2, D45.2, D46.2, D47.2, R2.6, R5.6, R13.6, R14.6, R15.6, R16.6, R17.6, R18.6, R19.6, R20.6, R21.6, R22.6, R23.6, R24.6, R25.6, R26.6, R27.6, R28.6, R29.6, R30.6, R31.6, R32.6, R33.6, R34.6, R35.6, R36.6, R37.6, R38.6, R39.6, R40.6, R41.6, R42.6, R43.6, R44.6, R45.6, R46.6
unnamed: D3.2, D48.2, D49.2, D50.2, D51.2, D52.2, D53.2, D54.2, D55.2, D56.2, D57.2, D58.2, D59.2, D60.2, D61.2, D62.2, D63.2, D64.2, D65.2, D66.2, D67.2, D68.2, D69.2, D70.2, D71.2, D72.2, D73.2, D74.2, D75.2, D76.2, D77.2, D78.2, D79.2, D80.2, D81.2, D82.2, R2.8, R5.8, R13.8, R14.8, R15.8, R16.8, R17.8, R18.8, R19.8, R20.8, R21.8, R22.8, R23.8, R24.8, R25.8, R26.8, R27.8, R28.8, R29.8, R30.8, R31.8, R32.8, R33.8, R34.8, R35.8, R36.8, R37.8, R38.8, R39.8, R40.8, R41.8, R42.8, R43.8, R44.8, R45.8, R46.8
unnamed: D4.2, D118.2, D119.2, D120.2, D121.2, D122.2, D123.2, D124.2, D125.2, D126.2, D127.2, D128.2, D129.2, D130.2, D131.2, D132.2, D133.2, D134.2, D135.2, D136.2, D137.2, D138.2, D139.2, D140.2, D141.2, D142.2, D143.2, D144.2, D145.2, D146.2, D147.2, D148.2, D149.2, D150.2, D151.2, D152.2, R2.7, R5.7, R13.7, R14.7, R15.7, R16.7, R17.7, R18.7, R19.7, R20.7, R21.7, R22.7, R23.7, R24.7, R25.7, R26.7, R27.7, R28.7, R29.7, R30.7, R31.7, R32.7, R33.7, R34.7, R35.7, R36.7, R37.7, R38.7, R39.7, R40.7, R41.7, R42.7, R43.7, R44.7, R45.7, R46.7
unnamed: D5.2, D161.2, D162.2, R3.2, R88.2, R89.2
unnamed: D6.2, D163.2, D164.2, R4.2, R86.2, R87.2
unnamed: D7.2, D165.2, D166.2, R6.2, R90.2, R91.2
unnamed: D8.2, D167.2, D168.2, R7.2, R92.2, R93.2
unnamed: D9.2, D159.2, D160.2, R8.2, R82.2, R83.2
unnamed: D10.2, D155.2, D156.2, R9.2, R84.2, R85.2
unnamed: D11.2, D157.2, D158.2, R11#2.2, R112.2, R113.2
unnamed: D12.2, D153.2, D154.2, R12.2, R116.2, R117.2
Ref: IC4.4, IC4.6, IC4.8, IC4.10, IC11.4, IC11.6, IC11.8, IC11.10, IC75.4, IC75.6, IC75.8, IC75.10, IC76.4, IC76.6, IC76.8, IC76.10, IC110.4, IC110.6, IC110.8, IC110.10, IC111.4, IC111.6, IC111.8, IC111.10, VR1.2

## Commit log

2016-02-28 :neckbeard: Added .gitattributes
2016-02-29 Preliminary Matrix Design
2016-02-29 Added touch detection
2016-02-29 Minor changes
2016-03-02 Increased array size, modified detector circuitry
2016-03-03 Completed layout of 2x2 LED cell
2016-03-03 Added detection circuitry
2016-03-03 Prepared for arraying
2016-03-03 Finished routing detector
2016-03-03 Prepare for arraying
2016-03-03 Additional cleanup
2016-03-03 Arrayed 2x2 LED cells
2016-03-03 Completed top row of detectors
2016-03-03 Completed left column detectors
2016-03-03 Located emitter diodes properly
2016-03-03 Routed reference voltage
2016-03-03 Set board edge
2016-03-03 Added text
2016-03-03 Generated gerbers
2016-03-03 Updated gerbers
2016-03-03 Minor changes and updates to schematic
